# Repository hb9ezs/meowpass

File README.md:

# MeowPass
**The ESP32-powered brain transplant for your PetSafe PetPorte.**

MeowPass is an open-source hardware and software replacement for the PetSafe PetPorte cat flap. By swapping the original PCB for a custom ESP32-C6 board running ESPHome, you gain full control via Home Assistant, easier cat management, and better reliability.

## Introduction
In the original Petporte cats can only be added by scanning them within 30 seconds of pressing a button. With a shy cat this can be difficult. 

I wanted to add a very shy cat to my cat flap, so I decided to create an ESPHome version and build MeowPass.

## Features
* Add cats by entering chip number + name in Home Assistant
* Track cats going through the cat flap
* Open / close the cat flap remotely
* See if any strange cats want to enter your home

## PCB Design
The custom PCB was designed in KiCad 9.0 to fit within the PetPorte chassis while accommodating the larger WL-134 module.

There are 3 different power levels: 
* 12V from the power supply, and to operate the solenoids
* 9V for the WL-134, this power needs to be as clean as possible to ensure maximum reading distance.
* 5V for the ESP32

The PCB was built with 4 layers: Signal - Gruond - Power - Ground

Layer 1, Signal:
Layer 2, Ground:
Layer 3, Power:
Layer 4, Ground:

This gives enough space to use wide power traces, and the ground planes don't need to be interrupted by signal or power traces. 

## Bill of Materials
* **Main Parts**
    * Seeed Studio XIAO ESP32C6
    * WL-134 RFID Reader
    * L293DNE Motor driver
    * MP1584EN 5V DC-DC Buck Converter
    * L7809CV Voltage Regulator 9V
* **Passives**
    * 3 x 100uF 25V Capacitor
    * 1 x 10uF Ceramic Capacitor
    * 1 x 1uF Ceramic Capacitor
    * 4 x 0.1uF Ceramic Capacitor
    * 1 x 47uH Inductor
    * 1 x 10kOhm Resistor
* **Connectors**
    * DC Power Jack Socket
    * KF2510 6-pin male connector
    * KF2510 2-pin male connector
<!-- TODO Photo of assembled print -->

A high quality 12V DC power supply is really important. I tested a cheaper power supply, and even with all the filtering this reduces the reading distance by a lot. For that reason i used a **MeanWell GST36E12-P1J**.

In total, I paid around 6$ per PCB, 14$ for the power supply and 32$ for all the other components, which gives a total of 52$ for the complete print. Additionally, the PetSafe Petporte costs around 120$ to 180$.

## Assembly instructions
The WL-134 needs an antenna with an inductance of around 500 uH to 600 uH. Even with the additional tuning capacitors the inductance of the existing antenna is too far off and doesn't work well with the WL-134. Fortunately, the WL-134 comes with its own antenna which has a matching inductance. You only need to solder a bit of cable with a KF2510 female connector to the antenna and install it in the existing antenna cover.

* Replace the existing RFID antenna with the 134 kHz that comes with the WL-134
* Unplug the cables from the existing PCB, and remove the PCB including the photo diode
* Install the MeowPass PCB, and connect the 6-pin connector for the solenoids
* Install the cat flap as usual
* The existing cover has a battery cover and doesn't fit over the larger PCB. For that reason you need to print a simplified cover, see [Printables](https://www.printables.com/model/1673473-petsafe-petporte-cover) or [Makerworld](https://makerworld.com/en/models/2626705-petsafe-petporte-cover)

## ESPHome Firmware
The ESPHome firmware needs the following files:
* [secrets.yaml](esphome/secrets.yaml) with SSID and password of your WiFi
* [std_includes.h](esphome/std_includes.h) to import cJSON.h
* [meowpass_common.yaml](esphome/meowpass_common.yaml) contains the main logic. This file does not contain any specific information like api keys, so you can use it multiple times if you create multiple MeowPass.
* [meowpass.yaml](esphome/meowpass.yaml) is the file that collects everything and needs to be flashed to the ESP32.

The firmware is built, so that the number of cats can change dynamically and can be added from Home Assistant. Cat data is stored as a JSON object in a persistent global variable (cat_db). The script parses this JSON using ESP-IDF’s native cJSON and looks up the scanned chip. There are 4 actions to modify the cat_db:
* `add_cat` with variables *chip*, *name* and *allowed* to add a new cat
* `remove_cat` with variable *name*, to remove the cat with the given name
* `set_allowed_true` with variable *name*
* `set_allowed_false` with variable *name*

> The cat_db has a `max_restore_data_length` of 254 bytes, which means that only the first 4 cats will be restored after a reboot. To store more than 4 cats some changes to the firmware need to be made.

You can set *allowed* to true or false, so that you can prevent entry for one cat without deleting the entry. All four of those actions have some error handling, so that the ESP32 shouldn't crash if the entry of an action is wrong.

Some additional features:
* `exit` can be set to *Open* or *Closed*
* `entry` can be set to *Open*, *Closed* or *Auto*. Only if this is set to *Auto* the chip scanning is relevant
* `opening_time` can be set to a value between 2 and 60 seconds. 

After a known chip is read, and this cat is set to allowed=true, the cat flap will open for the time defined in *opening_time*.

### WiFi connectivity
Where I wanted to install the MeowPass, the ESP32 had some WiFi connectivity issues.
To fix that, I connected an external WiFi antenna to the U.FL connector of the ESP32.

According to the [documentation for the XIAO ESP32C6](https://wiki.seeedstudio.com/xiao_esp32c6_getting_started/), `GPIO3` needs to be set to low to activate RF switch control, then `GPIO14` needs to be set to high to enable the external antenna.
To do so, add this code snippet to the ESPHome configuration:
```
switch:
  # Activate RF switch control
  - platform: gpio
    pin: GPIO3
    id: rf_switch_power
    internal: true
    restore_mode: ALWAYS_OFF

  # Use external antenna
  - platform: gpio
    pin: GPIO14
    id: antenna_selector
    internal: true
    restore_mode: ALWAYS_ON
```
For me, this increased the WiFi signal by around 15-20 dBm and solved all my issues.

## Home Assistant Dashboard

The main parts on the Home Assistant dashboard are a [Logbook card](https://github.com/royto/logbook-card) card that shows the most recent scans, and a Markdown table showing the registered cats.

The remaining cards to set the exit/entry mode or opening time are simple Tile cards.

### Logbook
The [Logbook card](https://github.com/royto/logbook-card) can be installed via HACS.

To use the logbook I have created an *Input text* helper called `input_text.meowpass_1_logbook` and an automation that will update this helper with the name + time whenever a cat is scanned.
```yaml
type: custom:logbook-card
entity: input_text.meowpass_1_logbook
hours_to_show: 24
show:
  state: true
  duration: false
  start_date: false
  end_date: false
  icon: true
  separator: false
  entity_name: true
custom_logs: false
title: MeowPass 1
desc: true
collapse: 5
state_map:
  - icon: mdi:rocket-launch
    icon_color: var(--accent-color)
    value: Regi *
  - icon: mdi:bomb
    icon_color: var(--primary-color)
    value: Ronja *
grid_options:
  rows: auto
  columns: 12
```

### Table
The table can be created with a Markdown card and some templating:
```yaml
type: markdown
content: >-
  {% set entries = states('sensor.meowpass_1_cat_database_readonly') | from_json %}

  | ID | Name | Status |

  | :--- | :--- | :--- |

  {% for id, info in entries.items() %}| {{ id }} | {{ info.name }} | {{ '✅
  Allowed' if info.allowed else '❌ Blocked' }} |

  {% endfor %}
```

## Possible improvements
* Without WiFi connection and a running Home Assistant the MeowPass still works, but cannot be controlled. This means if the WiFi connection drops, the cat flap can't be opened or closed.
In a future version I might consider using the existing buttons and LED or add some other control options.
* Currently the MeowPass can't differentiate between a cat coming in or going out. It would be cool to sense the direction of the cat and create some sort of presence monitor inside Home Assistant. 

## License
This project is licensed under the GPLv3 License. See the [LICENSE](LICENSE) file for details.

Essentially: You are free to use, modify, and distribute this project, but any derivative works must also be open-source under the same license.

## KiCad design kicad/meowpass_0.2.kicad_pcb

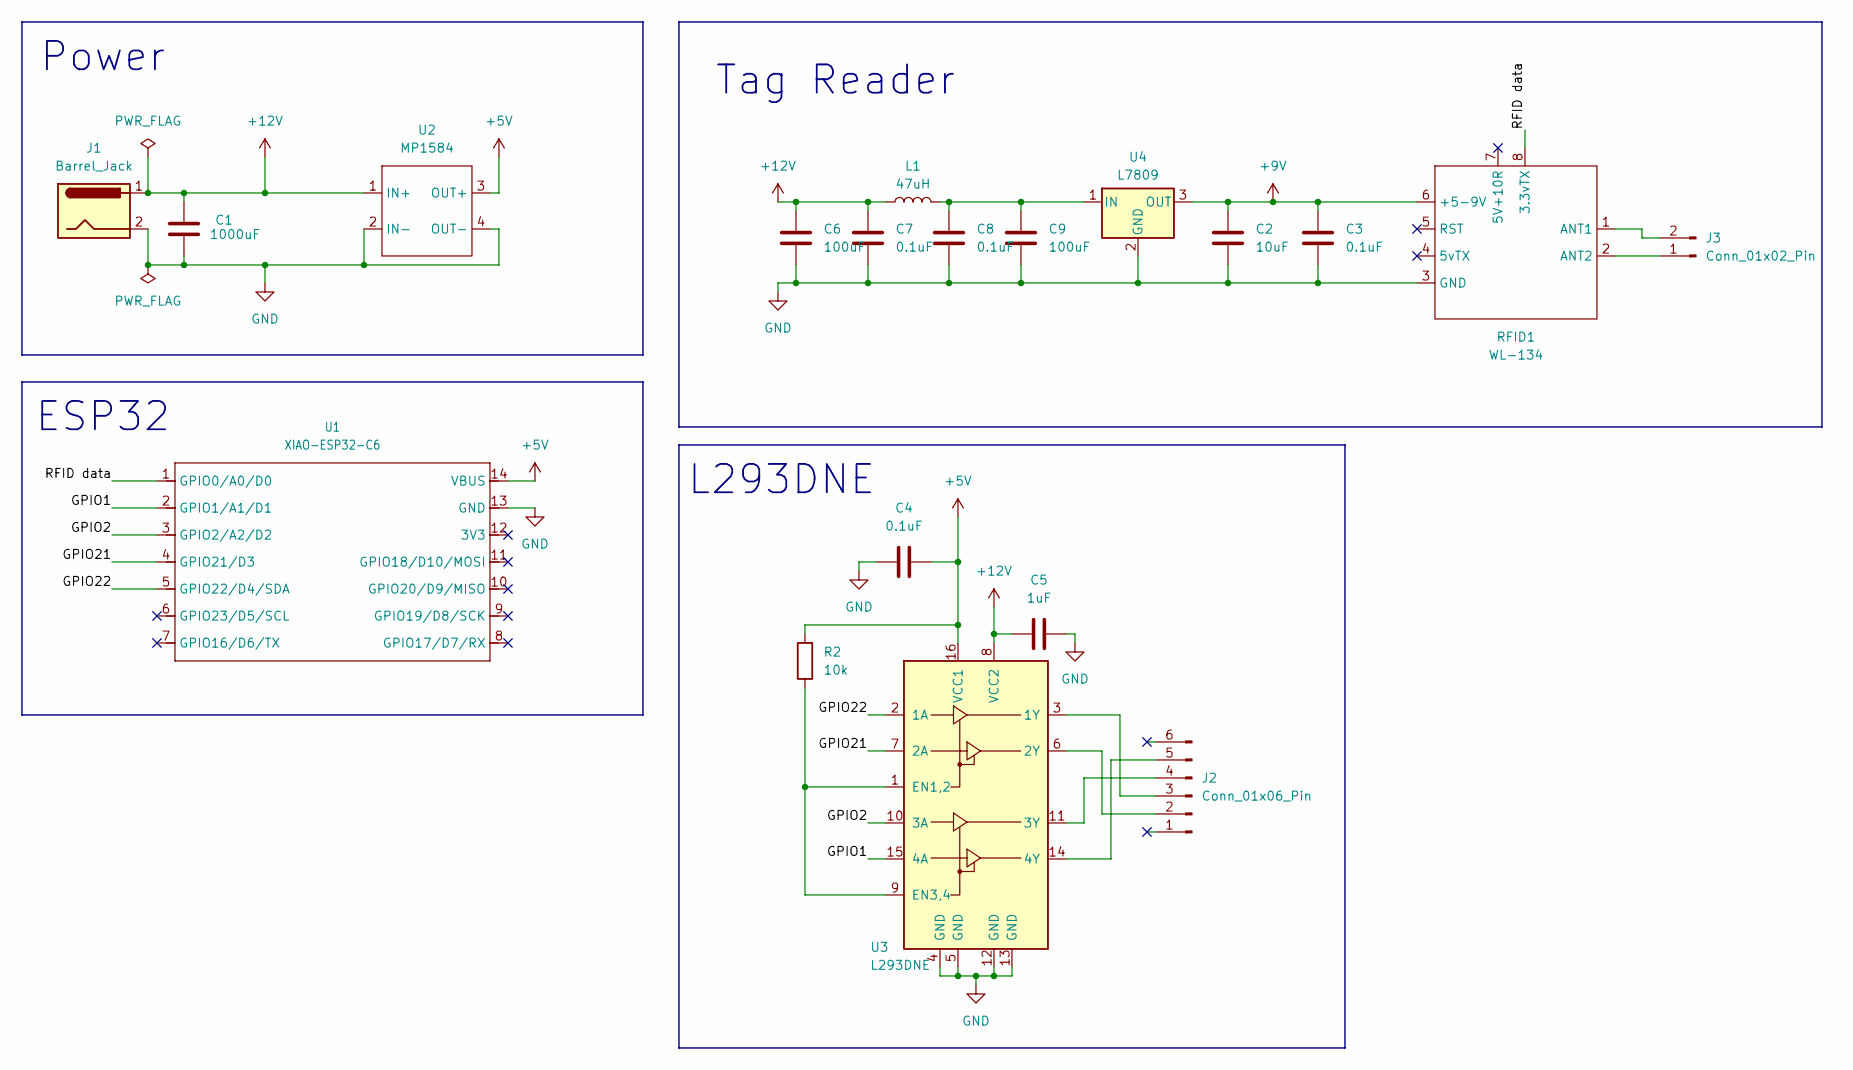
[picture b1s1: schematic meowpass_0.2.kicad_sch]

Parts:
C1: 1000uF; CP_Radial_D5.0mm_P2.00mm
C2: 10uF; C_Disc_D5.0mm_W2.5mm_P5.00mm
C3, C4, C7, C8: 0.1uF; C_Disc_D5.0mm_W2.5mm_P5.00mm
C5: 1uF; C_Disc_D5.0mm_W2.5mm_P5.00mm
C6, C9: 100uF; CP_Radial_D5.0mm_P2.00mm
J1: Barrel_Jack; BarrelJack_Horizontal
J2: Conn_01x06_Pin; Molex_KK-254_AE-6410-06A_1x06_P2.54mm_Vertical
J3: Conn_01x02_Pin; Molex_KK-254_AE-6410-02A_1x02_P2.54mm_Vertical
L1: 47uH; L_Radial_D8.7mm_P5.00mm_Fastron_07HCP
R2: 10k; R_Axial_DIN0207_L6.3mm_D2.5mm_P10.16mm_Horizontal
RFID1: WL-134
U1: XIAO-ESP32-C6; XIAO-ESP32C6-DIP
U2: MP1584; SRT_MPT1584EN_Module
U3: L293DNE; DIP-16_W7.62mm
U4: L7809; TO-220-3_Vertical

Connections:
+5V: C4.1, R2.2, U1.14 (VBUS), U2.3 (OUT+), U3.16 (VCC1)
+9V: C2.2, C3.2, RFID1.6 (+5-9V), U4.3 (OUT)
+12V: C1.1, C5.1, C6.1, C7.1, J1.1, L1.1, U2.1 (IN+), U3.8 (VCC2)
/GPIO1: U1.2 (GPIO1/A1/D1), U3.15 (4A)
/GPIO2: U1.3 (GPIO2/A2/D2), U3.10 (3A)
/GPIO21: U1.4 (GPIO21/D3), U3.7 (2A)
/GPIO22: U1.5 (GPIO22/D4/SDA), U3.2 (1A)
/RFID data: RFID1.8 (3.3vTX), U1.1 (GPIO0/A0/D0)
GND: C1.2, C2.1, C3.1, C4.2, C5.2, C6.2, C7.2, C8.2, C9.2, J1.2, RFID1.3 (GND), U1.13 (GND), U2.2 (IN-), U2.4 (OUT-), U3.4 (GND), U3.5 (GND), U3.12 (GND), U3.13 (GND), U4.2 (GND)
unnamed: J2.2, U3.6 (2Y)
unnamed: J2.3, U3.3 (1Y)
unnamed: J2.4, U3.11 (3Y)
unnamed: J2.5, U3.14 (4Y)
unnamed: J3.1, RFID1.2 (ANT2)
unnamed: J3.2, RFID1.1 (ANT1)
unnamed: R2.1, U3.1 (EN1,2), U3.9 (EN3,4)
unnamed: C8.1, C9.1, L1.2, U4.1 (IN)

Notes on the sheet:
ESP32
L293DNE
Power
Tag Reader

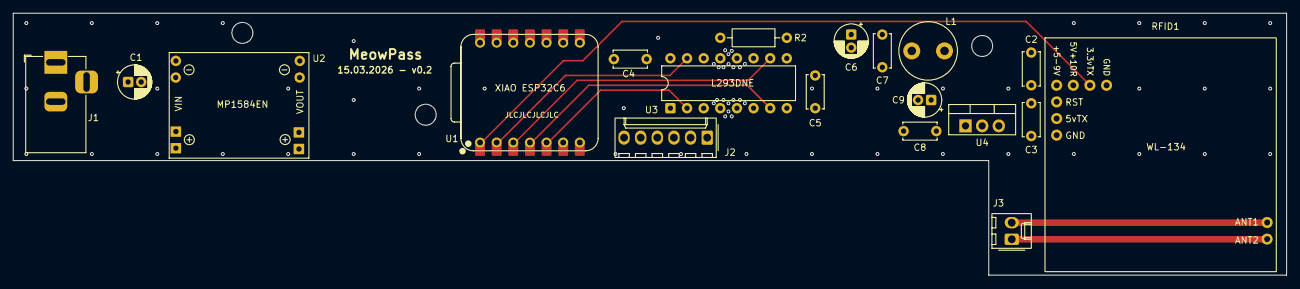
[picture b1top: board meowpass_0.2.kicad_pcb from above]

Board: 4 copper layers, 194.5 x 40.0 mm, 19 parts (0 on the bottom side), 17 nets.

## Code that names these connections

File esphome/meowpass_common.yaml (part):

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    id: ha_time
    
uart:
  - rx_pin: GPIO0
    baud_rate: 9600
    id: myuart0
    debug:
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  - platform: gpio
    id: output1
    pin: 
      number: GPIO1
      inverted: false

  - platform: gpio
    id: output2
    pin: 
      number: GPIO2
      inverted: false

  - platform: gpio
    id: output3
    pin: 
      number: GPIO21
      inverted: false

  - platform: gpio
    id: output4
    pin: 
      number: GPIO22
      inverted: false

  - platform: gpio
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
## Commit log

2026-04-02 added esphome files
2026-04-03 added kicad files + gerbers
2026-04-03 added screenshots of the pcb to images/
2026-04-03 added license file
2026-04-03 created the README, still needs some photos
2026-04-06 added some photos to README
2026-04-06 added links to printables and makerworld
2026-04-14 added some information regarding the HA dashboard
2026-04-14 added max_restore_data_length = 254
2026-04-18 added a section regarding WiFi connectivity
